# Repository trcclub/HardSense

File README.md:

# HardSense
Monitor local system sensors and display that data on a remote 2.8" LCD screen.
Full touch screen enabled.
Multiple screens including GPU details, CPU details

https://youtu.be/yXnQ3QwIAQI

The hardware monitoring is provided by the Open Hardware Monitor library:  https://github.com/openhardwaremonitor/openhardwaremonitor

NOTE:
To buld HardSenseESP, you need to change the partition scheme.

HardSenseESP Tools configuration settings:
	Board:  "ESP32 Dev Module"
	Partition Scheme: "HardSense ESP Partition"

In Arduino IDE, these are under the 'Tools' menu item.
In vMicro (Visual Micro for Visual Studio), they are under 'vMicro' menu item.

Essential bits: 
Bodmers TFT_ESPI:  https://github.com/Bodmer/TFT_eSPI

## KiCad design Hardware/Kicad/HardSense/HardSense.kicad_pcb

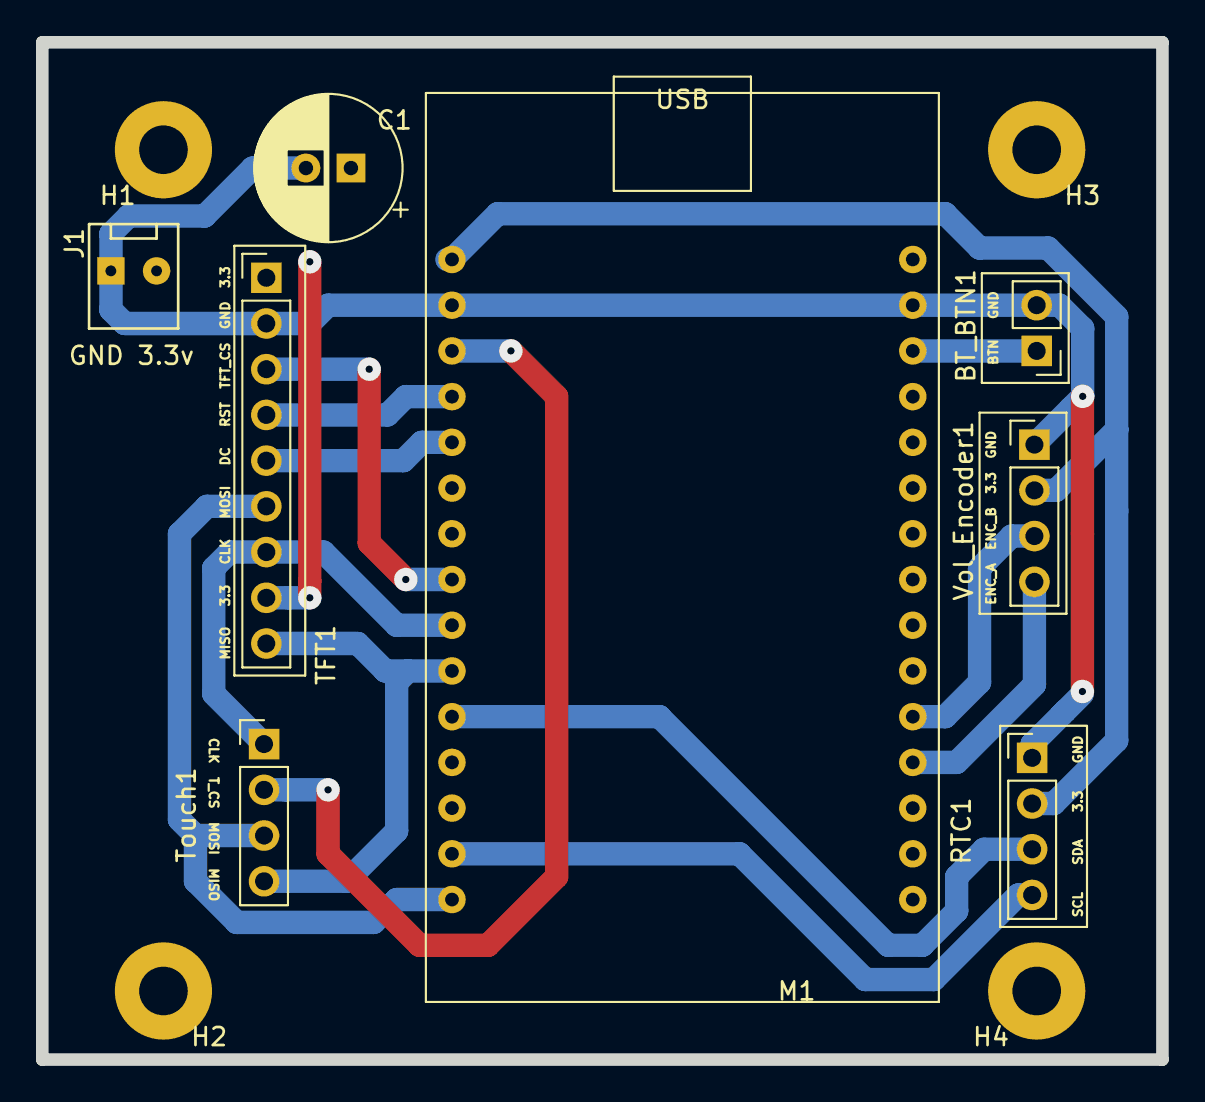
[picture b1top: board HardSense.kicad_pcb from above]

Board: 2 copper layers, 62.2 x 56.5 mm, 12 parts (0 on the bottom side), 14 nets.

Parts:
BT_BTN1: Conn_01x02; PinHeader_1x02_P2.54mm_Vertical
C1: 100uF; CP_Radial_D8.0mm_P2.50mm
H1, H2, H3, H4: MountingHole; MountingHole_2.7mm_Pad
J1: Conn_01x02; PinHeader_1x02_P2.54_Friction_Lock
M1: ESP32_DevKitC-30Pin; ESP32S_30Pin
RTC1: Conn_01x04; PinHeader_1x04_P2.54mm_Vertical
TFT1: Conn_01x09; PinHeader_1x09_P2.54mm_Vertical
Touch1: Conn_01x04; PinHeader_1x04_P2.54mm_Vertical
Vol_Encoder1: Conn_01x04; PinHeader_1x04_P2.54mm_Vertical

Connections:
3.3V: C1.1, J1.2, M1.1, RTC1.2, TFT1.1, TFT1.8, Vol_Encoder1.2
/BT_BTN: BT_BTN1.1, M1.28
/ENC_A: M1.19, Vol_Encoder1.4
/ENC_B: M1.20, Vol_Encoder1.3
/SCL: M1.14, RTC1.4
/SDA: M1.11, RTC1.3
/SPI_CLK: M1.9, TFT1.7, Touch1.1
/SPI_MISO: M1.10, TFT1.9, Touch1.4
/SPI_MOSI: M1.15, TFT1.6, Touch1.3
/TFT_CS: M1.8, TFT1.3
/TFT_DC: M1.5, TFT1.5
/TFT_RST: M1.4, TFT1.4
/T_CS: M1.3, Touch1.2
GND: BT_BTN1.2, C1.2, J1.1, M1.2, M1.29, RTC1.1, TFT1.2, Vol_Encoder1.1

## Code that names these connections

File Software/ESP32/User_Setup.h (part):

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// The DC (Data Command) pin may be labeled AO or RS (Register Select)
//
// With some displays such as the ILI9341 the TFT CS pin can be connected to GND if no more
// SPI devices (e.g. an SD Card) are connected, in this case comment out the #define TFT_CS
// line below so it is NOT defined. Other displays such at the ST7735 require the TFT CS pin
// to be toggled during setup, so in these cases the TFT_CS line must be defined and connected.
//
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// ###### EDIT THE PIN NUMBERS IN THE LINES FOLLOWING TO SUIT YOUR ESP8266 SETUP ######

// For NodeMCU - use pin numbers in the form PIN_Dx where Dx is the NodeMCU pin designation
#define TFT_CS   5  // Chip select control pin D8
#define TFT_DC   4  // Data Command control pin
#define TFT_RST  2  // Reset pin (could connect to NodeMCU RST, see next line)
//#define TFT_RST  -1    // Set TFT_RST to -1 if the display RESET is connected to NodeMCU RST or 3.3V

//#define TFT_BL PIN_D1  // LED back-light (only for ST7789 with backlight control pin)

#define TOUCH_CS 15     // Chip select pin (T_CS) of touch screen

//#define TFT_WR PIN_D2       // Write strobe for modified Raspberry Pi TFT only

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//#define TFT_SPI_OVERLAP

// In ESP8266 overlap mode the TFT chip select MUST connect to pin D3
//#define TFT_CS   PIN_D3
//#define TFT_DC   PIN_D5  // Data Command control pin
//#define TFT_RST  PIN_D4  // Reset pin (could connect to NodeMCU RST, see next line)
//#define TFT_RST  -1  // Set TFT_RST to -1 if the display RESET is connected to NodeMCU RST or 3.3V


// ###### EDIT THE PIN NUMBERS IN THE LINES FOLLOWING TO SUIT YOUR ESP32 SETUP   ######
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//#define TFT_MISO 19
//#define TFT_MOSI 23
//#define TFT_SCLK 18
//#define TFT_CS   15  // Chip select control pin
//#define TFT_DC    2  // Data Command control pin
//#define TFT_RST   4  // Reset pin (could connect to RST pin)
//#define TFT_RST  -1  // Set TFT_RST to -1 if display RESET is connected to ESP32 board RST

//#define TFT_BL   32  // LED back-light (only for ST7789 with backlight control pin)

//#define TOUCH_CS 21     // Chip select pin (T_CS) of touch screen

//#define TFT_WR 22    // Write strobe for modified Raspberry Pi TFT only

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//#define TFT_MISO 19
//#define TFT_MOSI 23
//#define TFT_SCLK 18
//#define TFT_CS   14  // Chip select control pin
//#define TFT_DC   27  // Data Command control pin
//#define TFT_RST  33  // Reset pin (could connect to Arduino RESET pin)
//#define TFT_BL   32  // LED back-light (required for M5Stack)

// ######       EDIT THE PINs BELOW TO SUIT YOUR ESP32 PARALLEL TFT SETUP        ######
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//#define ESP32_PARALLEL

// The ESP32 and TFT the pins used for testing are:
//#define TFT_CS   33  // Chip select control pin (library pulls permanently low
//#define TFT_DC   15  // Data Command control pin - must use a pin in the range 0-31
//#define TFT_RST  32  // Reset pin, toggles on startup

//#define TFT_WR    4  // Write strobe control pin - must use a pin in the range 0-31
//#define TFT_RD    2  // Read strobe control pin
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
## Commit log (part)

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2019-09-28 Initial commit of the Windows software for HardSense.
2019-09-30 Adding initial application icon (blank). Made application a trayicon app and change the form close behaviour to minimize
2019-10-01 Added the beginnings of pulling data.
2019-10-04 The beginnings of the monitor class. Also created the NetSpeedMonitor class.
2019-10-05 Adding my modified version of the openhardwaremonitor. I've added a new value the SensorType enum for 'BPS' This is to handle the 'Bytes Per Second' value from the NIC Interfaces.
2019-10-06 Renamed the MMFIle to HardSenseMemFile and added a project settings for the filename. Made all the appropriate member properties and methods static to allow read access to the data without needing an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
2019-10-06 Fixed some bugs
2019-10-06 Added a couple more property settings for default values.
2019-10-06 Added an about box because I felt like doing something different for a while.
2019-10-07 Not sure if __vm folder should be included or not. So, I'm including it just to be safe.
2019-10-07 Did some refactoring as I need to get the Hardware items Name into the senor item. This is really helpfull for knowing the HDD logical drive identifer (C:, G:, F:, ...) and which sensor is for which 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
2019-10-08 Rudimentary socket server.
2019-10-08 Commit a working server before continuing again.
2019-10-08 Added the Sender object to the DataStreamer.
2019-10-08 Fixed the DataStreamer threadproc method to join the existing threads instead of spinning on it's own thread.
2019-10-09 Added a heartbeat to the datastreamer. This way the server can disconnect and properly close the sockets if the client has stopped responding (disconnected)
2019-10-09 Some small refactoring
2019-10-09 Comitting before continuing.
2019-10-11 Refactored the communication protocol and the way the data is read on the Bluetooth serial input. Refactored all the transmission key names.
2019-10-11 Mostly completed the Bluetooth configurator. Enough to merge back into master before taking the next steps.
2019-10-11 Moving some files around
2019-10-11 Remove old class.
2019-10-11 try again.
2019-10-12 Still moving things around
2019-10-12 Another small change
2019-10-12 Finally have a working Bluetooth based settings updater. That was a lot of work.
2019-10-13 Fixed a bug for the Wifi read/write data. Updated to new format. Added beginnnig of socket data streaming.
2019-10-13 Forget to reenable the display output in the last commit.
2019-10-14 Some updates.
2019-10-14 Commit the beginnigs of the display handler. My idea seems to work so far, but let's see what happens when I scale it up.
2019-10-15 Added mutexes around accessing the Display and Output Queue objects. Also added mutex around the actual OutputData and changed the HandleOoutput a bit. Startd to add a heartbeat and a way to reconnec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
2019-10-15 Add initial Bluetooth Configurator screen to HardSenseESP. Also did a bit of refactoring.
2019-10-15 Small bit of refactoring.
2019-10-15 Progress has been acheived! Commit my first working widget! A dial. And put it on the home screen for the CPU load.
2019-10-16 Added new fonts. Small bit of refactoring including a bit more error handling.
2019-10-16 New Widget Base Class for loading fonts and handling common widget work.
2019-10-16 Removed the old screen managment functions. They've been replaced with a new strategy using classes.
2019-10-17 Some refactoring and trying to fix a bug. I've got one fixed. looking for more.
2019-10-17 Added touch controller. It seems to work.
2019-10-18 Added some of the GPU Panel on the home screen. My idea about using classes and function pointers seems to be bearing fruit.
2019-10-18 Reverting I hope
2019-10-18 I don't even know anymore.
2019-10-18 stuff is broken all over
2019-10-18 I'm never going to fix this stupid git fuck up am i.
2019-10-18 fuck!
2019-10-18 Added start of GPU panel (again)
2019-10-18 Completed the GPU panel on the home screen
2019-10-18 Add the Net panel to home screen.
2019-10-18 Begin on the Ram panel.
2019-10-19 I'm relativly sure that I've fixed a bug or two now. The onTimer() was doing way to much work. Plush, the HSSerial function it calls also needed to be IRAM_ATTR
    Also started updating the home screen with the use of a sprite to update the text.
2019-10-19 small refactor. ensured connectedToSomething is false when startnig the Bluetooth handler.
2019-10-19 Cleaned up commented out code.
2019-10-19 Comleted the Ram panel on the home screen.
2019-10-20 Fixed the DrawBoxWithBorderAndDropShadow() method to no longer draw the box 1 pixel too wide and too high. Refactored HSSerial a bit to use TRANS_KEY instead of char
2019-10-20 Try to put some of the code back to where it was before that last push. I don't understand this really weird bug in TFT_eSpi.
2019-10-21 Refactored Home Screen to use a better relative coordiante system when plotting stuff onto the screen.
    Added the Time panel to the home screen.
    Added a new UpdateScreenOnInterval handler.
2019-10-21 Added abilit to update the time on HardSenseESP through the Bluetooth Configurator.
2019-10-21 Adding new GameScreen.
2019-10-22 Created a stand alone netpanel class so I can re-use it on the Game screen.
2019-10-23 I seem to have a working graph for GPU temperature and fan load. Have added it to the Game screen now.
2019-10-23 Add a load dial to the Game screen. I'm going to change this 'Game' screen to become the 'VideoCard' screen going forward though and will make a new 'Game' screen with different panels and widgets.
2019-10-23 Add new memPanel with 2 sizes.
2019-10-23 Fixed a couple bugs in the memPanel. Don't use transparent background when trying to overwrite an area. It just doesn't work eh.
2019-10-24 Finally found the bug that was causing the Dial's to stop working and fixed it. Change the way the TFT is passed into widget class and used. It's now a pointer. Refactored the Screen drawbox func to 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
2019-10-27 Increased the stack size of the DisplayHandler task. I finally caught one of the infrequent crashes in the serial monitor: "Stack smashing protect failure!".
2019-10-28 Tried to clean up the code a bit by removing seemingly unnecessary calls to yield(). Removed unusded font file. The screen has been running for quite a while on the Games screen now and has not gone 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
2019-10-30 Adding initial Kicad project for circuit boards.
2019-10-31 Add FPS counter Hardware item and Sensor to the list of available sensors. Next is to buld the FPS montior itself. Add a 'FPS' type to the SensorType. At least for now. I might change this to one of 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
2019-11-01 Fixed a couple bugs with how the time is set and read. Little bit of refactoring.
2019-11-04 Added a FPS monitor.
2019-11-05 Some refactoring to clean up the code a bit.
2019-11-05 Changed the number of frames used to calculate the FPS. It still isn't great, but it's not horrible.
2019-11-05 Added a CPU load panel to the Game Screen
2019-11-05 Commit initial CPU Details screen. This sceen is displays when the user toches the CPU panel on the Home Screen.
2019-11-20 Most of a working CPU Details screen.
2019-11-25 I have a working CPU Details screen, but I'm still un-happy with the flickering on updates.
2019-11-27 Just a small change to help in debugging the screen blanking problem.
2019-11-29 Fixed a bug where the amount of free system ram was ending up being used as the C: drive free space value (missed a break in the case statement)
2019-12-02 Add a couple of yeild() calls back. Since removing them, I started to see inexplicable crashes which seemed to point to clearing a counter in the task.
2019-12-02 Added a couple of yeilds() back into the DisplayHandler as I was starting to see watchdog timer errors. I've now been runing HardSenseESP for many hours without a single problem All seems well now. H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
    Also began to add the new SplashScreen, but I think I need to re-think how to do that. Sadness.
2020-02-06 Removing HardSenseESP from the Visual Studio Project. A new VSCode project will be checked in soon.
2020-02-06 Adding HardSenseESP as a VSCode project
2020-02-06 Moved the btButton (BlueTooth button) to GPIO 37 to accommodate a better trace on the final PCB.
2020-02-07 Removed unused includes from QueueItem.h
2020-02-11 Start to change over DisplayManager LoadNewScreen to use the Enum values better(ish)
2020-02-12 Added bluetoothc configuration display screen.
2020-02-12 Adding bluetooth configuration display screen and some refactoring around the display hanlders use of the ScreenTypes enum.
2020-02-13 Adding initial SplashScreen
2020-02-13 Added the Server box to the SplashScreen
2020-02-13 Initial Commit for this branch. Need to fix the Bluetooth display screen.
2020-02-13 Added wifi and bluetooth device IDs to the hardsens.txt configuration file.
    Fixed bug in Displaying labels on the Bluetooth configurator screen.
2020-02-13 Added new DeviceID panel to the Bluetooth Configurator Screen.
2020-02-14 Updates for spiffs size
2020-02-14 Trying to undo the things I did in the last changes. I didn't realize I was still in master. Oops.
2020-02-14 Adding initial partition file (copied from min_spiffs.cxv) Updating readme.txt
2020-02-14 Add a few print statmeents in attempt to localize a memory leak
2020-02-14 Adding new partition file and instructions. New font files are smaller.
2020-02-15 Starting to add OTA code to the bluetooth configurator screen.
2020-02-15 Refactored the way the queues are used. This was big.
2020-02-15 Added the new cpp file. This was missed earlier. oops.
2020-02-16 Added basic OTA functionality. It works!
2020-02-16 Adding initial feedback mechanism for updating the display during the ArduinoOTA process.
2020-02-16 Adding image about OTA updates.
2020-02-17 I think I finally found a fix for the problem where a screen would load, then the numbers displayed would go high out of range. This bug was most noticable when tranisition from the home screen to th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
2020-02-17 Just a bit of tiddying up. Updated readme as well.
2020-02-17 A bit more clean up.
2020-02-18 New PCB board for HardSense
2020-02-18 Add some images of the PCB board.
2020-02-18 Added the printable PCB file
2020-02-18 Some minor updates to the pcb
    Moving stuff around as I'm going to create a new KiCad project for the
    NodeMCU-32S board
2020-02-19 New KiCad schematic and PCB for ESP32S based system. Updated code with new pin mappings for ESP32S based sytem.
2020-02-19 Adding PDF files for the top, bottom, and combined copper layers of the PCB board.
2020-02-20 Updates to PCB board. Changed pin connections from ESP32S to TFT in order to get a better trace line on the PCB.
2020-02-20 Final PCB design for ESP32S based HardSenseESP.
2020-02-21 Fixed the pin mapping to the TFT. I had it wrong and the PCB didn't work. After fixing the pin mapping, all is well.
2020-02-24 Add ability to set the time when HardSenseESP connects to the server.
2020-02-25 Updated icon and program name for the Windows application. It's now officially called HardSense64
2020-02-26 Change the tooltip of the HardSense64 tray icon to use 'HardSense64'
2020-03-01 Add a few images and modify the readme.
2020-03-01 2.8"
2020-03-11 New User_Setup.h file for use with TFT_eSPI version Fixed text bug on Bluetooth configurator screen as best I can for now.
2020-03-11 Fix small bug with font in the time box on home screen.
2020-03-12 REFACTOR: removed the whole PROTOOLKEY fiasco. Now using only the TRANS__KEY enum to do it all.
2020-03-14 Many updates.
